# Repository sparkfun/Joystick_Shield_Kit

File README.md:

SparkFun Joystick Shield Kit
========================================

[*SparkFun Joystick Shield Kit (DEV-09760)*](https://www.sparkfun.com/products/9760)

The SparkFun Joystick Shield Kit contains all the parts you need to enable your Arduino with a joystick! 
The shield sits on top of your Arduino and turns it into a simple controller. 
Five momentary push buttons (4+ joystick select button) and a two-axis thumb joystick gives your Arduino functionality on the level of old Nintendo controllers. 

Repository Contents
-------------------

* **/Firmware** - Example code 
* **/Hardware** - Eagle design files (.brd, .sch)
* **/Production** - Production panel files (.brd)

Documentation
--------------
* **[Hookup Guide](https://www.sparkfun.com/tutorials/161)** - Basic hookup guide for the Joystick Shield.
* **[Quickstart Guide](http://www.sparkfun.com/commerce/tutorial_info.php?tutorials_id=171)** - Quickstart guide using Arduino and Processing.
* **[SparkFun Fritzing repo](https://github.com/sparkfun/Fritzing_Parts)** - Fritzing diagrams for SparkFun products.
* **[SparkFun 3D Model repo](https://github.com/sparkfun/3D_Models)** - 3D models of SparkFun products. 

License Information
-------------------
This product is _**open source**_! 

The **hardware** is released under [Creative Commons ShareAlike 4.0 International](https://creativecommons.org/licenses/by-sa/4.0/).

The **code** is beerware; if you see me (or any other SparkFun employee) at the local, and you've found our code helpful, please buy us a round!

Please use, reuse, and modify these files as you see fit. Please maintain attribution to SparkFun Electronics and release anything derivative under the same license.

Distributed as-is; no warranty is given.

- Your friends at SparkFun.

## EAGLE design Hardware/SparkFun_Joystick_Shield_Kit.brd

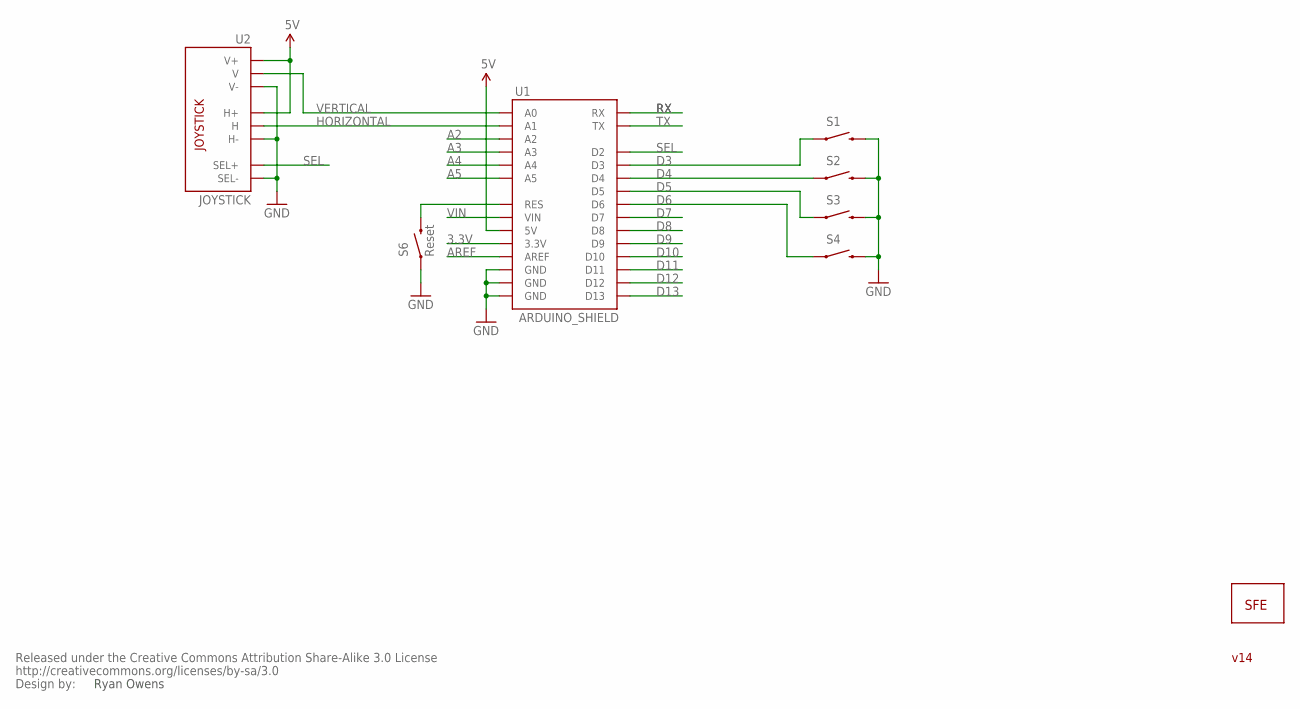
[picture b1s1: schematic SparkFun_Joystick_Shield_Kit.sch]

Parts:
JP1: LOGO-SFENEW; SFE-NEW-WEBLOGO
S1, S2, S3, S4: SWITCH-MOMENTARY-212MM; TACTILE-PTH-12MM
S6: Reset; TACTILE-PTH
U1: ARDUINO_SHIELD; DUEMILANOVE_SHIELD
U2: JOYSTICK
U$3: CREATIVE_COMMONS

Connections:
3.3V: U1.3.3V
5V: U1.5V, U2.H1 (H+), U2.V1 (V+)
A2: U1.A2
A3: U1.A3
A4: U1.A4
A5: U1.A5
AREF: U1.AREF
D3: S1.1, U1.D3
D4: S2.1, U1.D4
D5: S3.1, U1.D5
D6: S4.1, U1.D6
D7: U1.D7
D8: U1.D8
D9: U1.D9
D10: U1.D10
D11: U1.D11
D12: U1.D12
D13: U1.D13
GND: S1.3 (2), S2.3 (2), S3.3 (2), S4.3 (2), S6.1, U1.GND@0 (GND), U1.GND@1 (GND), U1.GND@2 (GND), U2.B2A (SEL-), U2.H3 (H-), U2.V3 (V-)
HORIZONTAL: U1.A1, U2.H2 (H)
unnamed: S6.3 (2), U1.RES
RX: U1.RX
SEL: U1.D2, U2.B1A (SEL+)
TX: U1.TX
VERTICAL: U1.A0, U2.V2 (V)
VIN: U1.VIN

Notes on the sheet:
Ryan Owens
v14

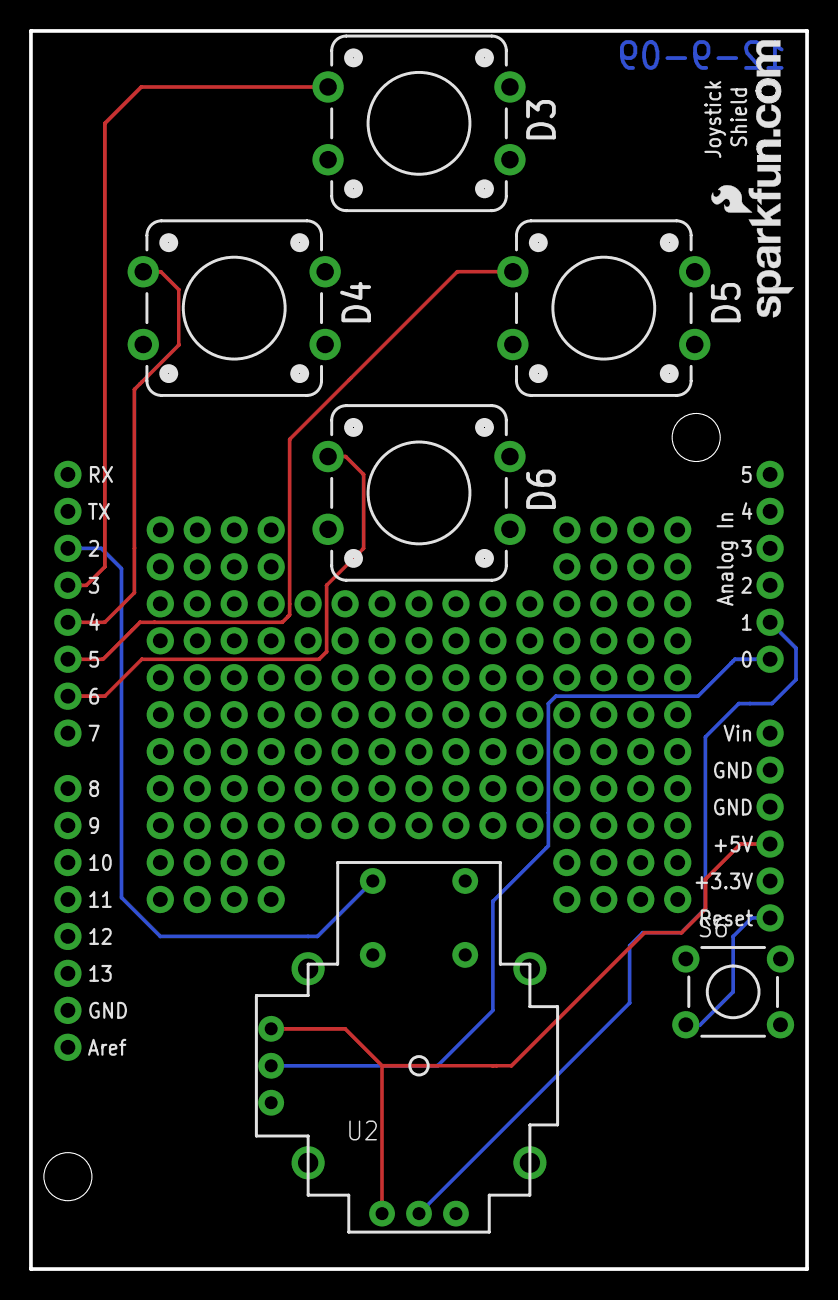
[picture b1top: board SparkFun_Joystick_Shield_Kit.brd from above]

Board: 2 copper layers, 53.3 x 85.1 mm, 9 parts (0 on the bottom side), 10 nets.

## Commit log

2015-05-05 Adding hardware, updating READMEs, adding example sketch
2019-02-20 Arduino and Processing Examples
    Include Joystick Arduino and Processing Examples
2019-02-21 Default Element in Array
    Adjust element to 0 for default COM port in Array

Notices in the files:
parts and their libraries:
SparkFun: Released under the Creative Commons Attribution Share-Alike 3.0 License
SparkFun: http://creativecommons.org/licenses/by-sa/3.0
